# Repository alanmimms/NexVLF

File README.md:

# NexVLF
This is software defined radio hardware and software for VLF 40kHz to
300kHz range with high noise immunity, dynamic range, sensitivity, and
a built in 1m diameter loop antenna. It could be used to fool around
with VLF, to add a WWVB decoder to your shack (one is planned in
software), or whatever you like.

# Architecture

NexVLF uses an STM32H753 microcontroller to control and shovel bits
from the AK5572 24-bit audio codec into a USB2 (480Mb/s "high speed")
audio interface. A host CPU runs an app built for Linux, MacOS, and
Windows supplying the DSP functions to demodulate and tune the SDR
samples and a flexible and easily extensible receiver GUI mostly
written in Lua.

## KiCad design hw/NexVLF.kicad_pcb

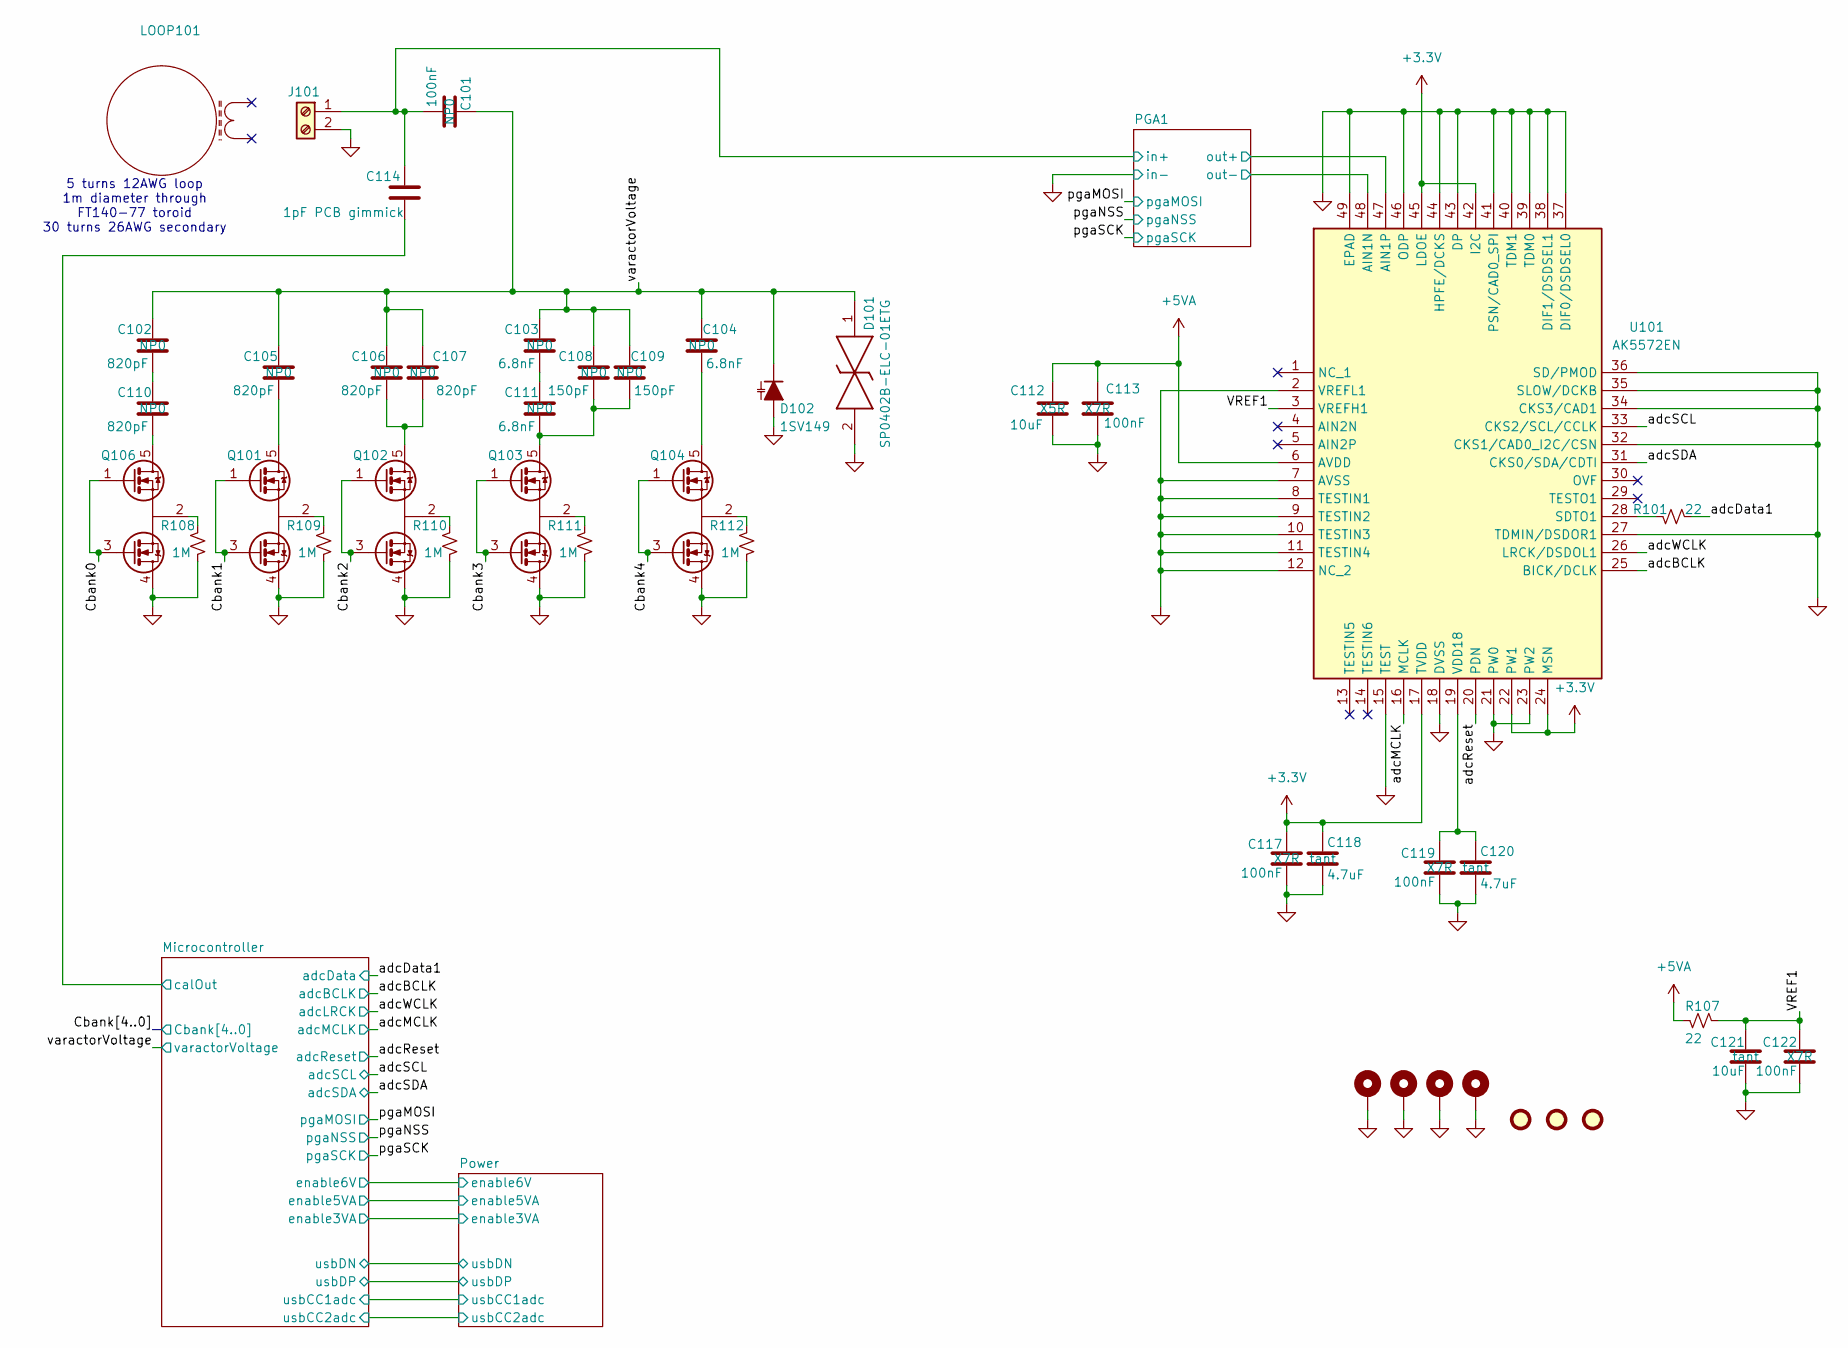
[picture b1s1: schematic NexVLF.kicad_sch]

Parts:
C101: 100nF; C_1206_3216Metric; MPN GRM3195C2A104JA01D; LCSC_PN C170182
C102, C105, C106, C107, C110: 820pF; C_1206_3216Metric; MPN GRM3195C2A104JA01D; LCSC_PN C170182
C103, C104, C111: 6.8nF; C_1206_3216Metric; MPN GRM3195C2A104JA01D; LCSC_PN C170182
C108, C109: 150pF; C_1206_3216Metric; MPN GRM3195C2A104JA01D; LCSC_PN C170182
C112: 10uF; C_0402_1005Metric; MPN GRM155R61E105KE11D; LCSC_PN C301928
C113, C117, C119, C122: 100nF; C_0402_1005Metric; MPN C0805F104K1RACAUTO; LCSC_PN C24452
C114: 1pF PCB gimmick; PCB-gimmick-1pF
C118, C120: 4.7uF; C_0805_2012Metric; MPN 298D475X9010M2T; LCSC_PN C18535241
C121: 10uF; C_0805_2012Metric; MPN TAJD106K050RNJ; LCSC_PN C4983748
D101: SP0402B-ELC-01ETG; D_0402_1005Metric; MPN SP0402B-ELC-01ETG; LCSC_PN C1974049
D102: 1SV149; TO-92-2
FID101, FID102, FID103: Fiducial; Fiducial_0.5mm_Mask1.5mm
H101, H102, H103, H104: MountingHole_Pad; MountingHole_3.2mm_M3_DIN965_Pad
J101: ANT; Altech_AK300_1x02_P5.00mm_45-Degree
LOOP101: (no value)
Q101, Q102, Q103, Q104, Q106: DMN32D2LDF; SOT-353_SC-70-5
R101, R107: 22; R_0402_1005Metric; JLCPCBpn C4258780
R108, R109, R110, R111, R112: 1M; R_0402_1005Metric; JLCPCBpn C4258780
U101: AK5572EN; QFN50P700X700X100-49N-D; Mouser Part Number 412-AK5572EN

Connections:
+3.3V: C117.2, C118.2, U101.17 (TVDD), U101.22 (PW1), U101.24 (MSN), U101.42 (I2C), U101.45 (LDOE); also elsewhere on the board
+5VA: C112.1, C113.1, R107.2, U101.6 (AVDD); also elsewhere on the board
/Cbank0: Q106.1 (G1), Q106.3 (G2); also elsewhere on the board
/Cbank1: Q101.1 (G1), Q101.3 (G2); also elsewhere on the board
/Cbank2: Q102.1 (G1), Q102.3 (G2); also elsewhere on the board
/Cbank3: Q103.1 (G1), Q103.3 (G2); also elsewhere on the board
/Cbank4: Q104.1 (G1), Q104.3 (G2); also elsewhere on the board
/PGA1/in+: C101.2, C114.1, J101.1; also elsewhere on the board
/PGA1/out+: U101.47 (AIN1P); also elsewhere on the board
/PGA1/out-: U101.48 (AIN1N); also elsewhere on the board
/VREF1: C121.1, C122.1, R107.1, U101.3 (VREFH1)
/adcBCLK: U101.25 (BICK/DCLK); also elsewhere on the board
/adcData1: R101.1; also elsewhere on the board
/adcMCLK: U101.16 (MCLK); also elsewhere on the board
/adcReset: U101.20 (PDN); also elsewhere on the board
/adcSCL: U101.33 (CKS2/SCL/CCLK); also elsewhere on the board
/adcSDA: U101.31 (CKS0/SDA/CDTI); also elsewhere on the board
/adcWCLK: U101.26 (LRCK/DSDOL1); also elsewhere on the board
/varactorVoltage: C101.1, C102.1, C103.1, C104.1, C105.1, C106.1, C107.1, C108.1, C109.1, D101.1, D102.1 (K); also elsewhere on the board
GND: C112.2, C113.2, C117.1, C118.1, C119.1, C120.1, C121.2, C122.2, D101.2, D102.2 (A), H101.1, H102.1, H103.1, H104.1, J101.2, Q101.4 (D2), Q102.4 (D2), Q103.4 (D2), Q104.4 (D2), Q106.4 (D2), R108.2, R109.2, R110.2, R111.2, R112.2, U101.2 (VREFL1), U101.7 (AVSS), U101.8 (TESTIN1), U101.9 (TESTIN2), U101.10 (TESTIN3), U101.11 (TESTIN4), U101.12 (NC_2), U101.15 (TEST), U101.18 (DVSS), U101.21 (PW0), U101.23 (PW2), U101.27 (TDMIN/DSDOR1), U101.32 (CKS1/CAD0_I2C/CSN), U101.34 (CKS3/CAD1), U101.35 (SLOW/DCKB), U101.36 (SD/PMOD), U101.37 (DIF0/DSDSEL0), U101.38 (DIF1/DSDSEL1), U101.39 (TDM0), U101.40 (TDM1), U101.41 (PSN/CAD0_SPI), U101.43 (DP), U101.44 (HPFE/DCKS), U101.46 (ODP), U101.49 (EPAD); also elsewhere on the board
unnamed: C102.2, C110.1
unnamed: C103.2, C111.1
unnamed: C105.2, Q101.5 (D1)
unnamed: Q101.2 (S), R109.1
unnamed: C106.2, C107.2, Q102.5 (D1)
unnamed: Q102.2 (S), R110.1
unnamed: C108.2, C109.2, C111.2, Q103.5 (D1)
unnamed: Q103.2 (S), R111.1
unnamed: C104.2, Q104.5 (D1)
unnamed: Q104.2 (S), R112.1
unnamed: C110.2, Q106.5 (D1)
unnamed: Q106.2 (S), R108.1
unnamed: R101.2, U101.28 (SDTO1)
unnamed: C119.2, C120.2, U101.19 (VDD18)

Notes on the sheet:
5 turns 12AWG loop 1m diameter through FT140-77 toroid 30 turns 26AWG secondary

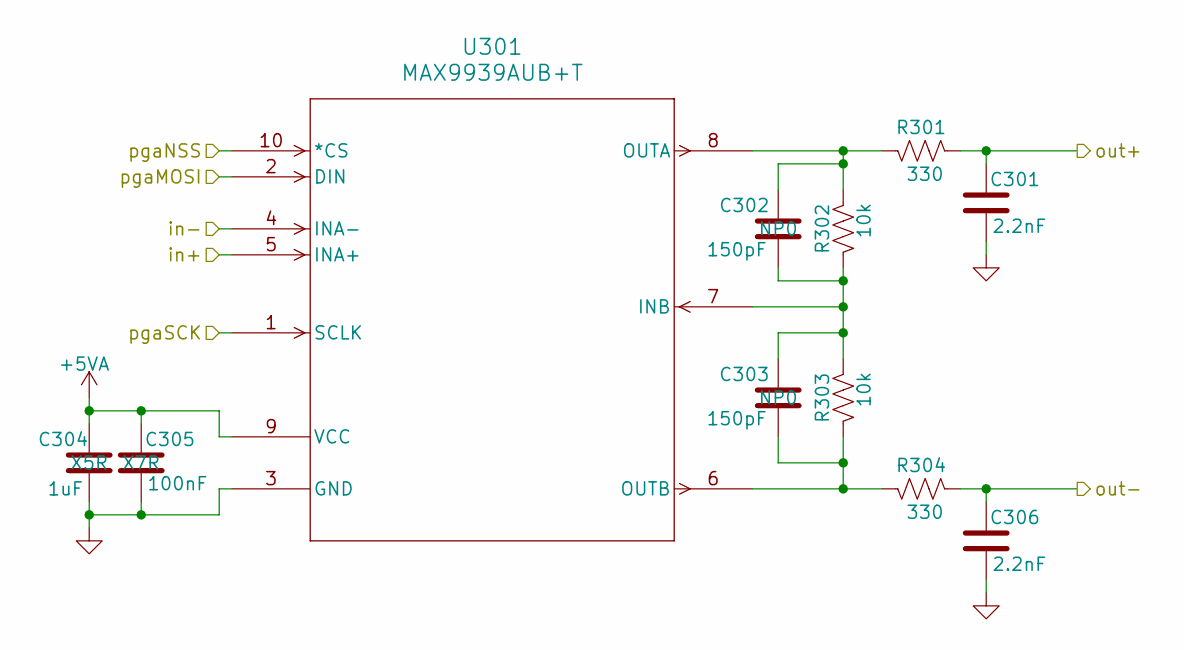
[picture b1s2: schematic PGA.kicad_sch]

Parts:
C301, C306: 2.2nF; C_0603_1608Metric
C302, C303: 150pF; C_0603_1608Metric; MPN 06033A151FAT2A; LCSC_PN C107038
C304: 1uF; C_0402_1005Metric; MPN GRM155R61E105KE11D; LCSC_PN C301928
C305: 100nF; C_0402_1005Metric; MPN C0805F104K1RACAUTO; LCSC_PN C24452
R301, R304: 330; R_0402_1005Metric; LCSC_PN C854274
R302, R303: 10k; R_0402_1005Metric; JLCPCBpn C723366
U301: MAX9939AUB+T; SOP50P490X110-10N; LCSC_PN C2057611

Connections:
+5VA: C304.1, C305.1, U301.9 (VCC); also elsewhere on the board
/PGA1/in+: U301.5 (INA+); also elsewhere on the board
/PGA1/out+: C301.1, R301.2; also elsewhere on the board
/PGA1/out-: C306.1, R304.2; also elsewhere on the board
/pgaMOSI: U301.2 (DIN); also elsewhere on the board
/pgaNSS: U301.10 (*CS); also elsewhere on the board
/pgaSCK: U301.1 (SCLK); also elsewhere on the board
GND: C301.2, C304.2, C305.2, C306.2, U301.3 (GND), U301.4 (INA-); also elsewhere on the board
unnamed: C302.2, C303.1, R302.2, R303.1, U301.7 (INB)
unnamed: C302.1, R301.1, R302.1, U301.8 (OUTA)
unnamed: C303.2, R303.2, R304.1, U301.6 (OUTB)

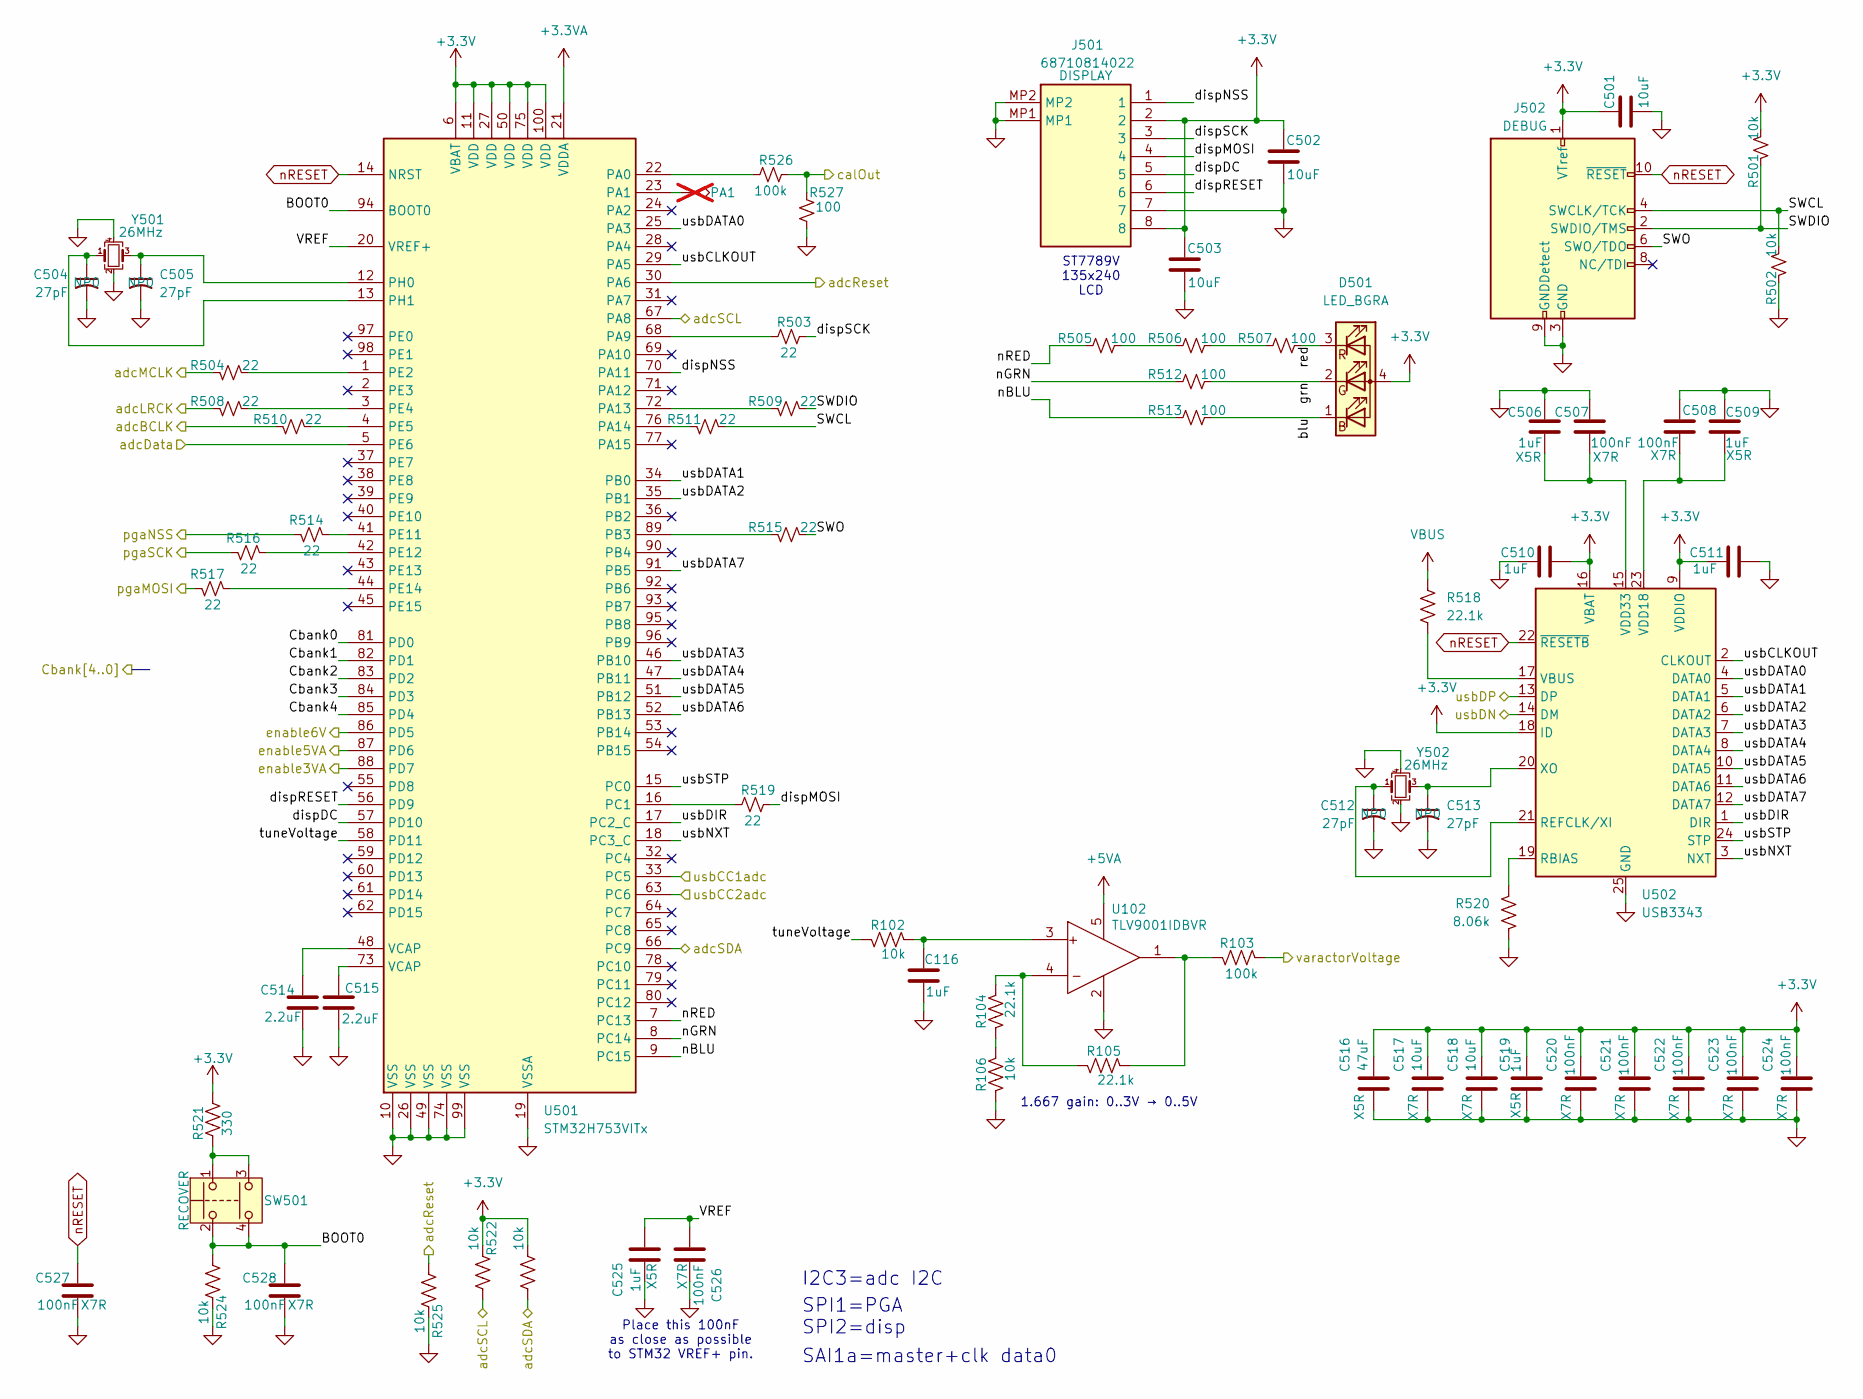
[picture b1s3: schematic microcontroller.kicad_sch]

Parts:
C116, C506, C509, C510, C511: 1uF; C_0402_1005Metric; Manufacturer_Part_Number GRM155R61E105KE11D; Mouser Part Number 81-GRM155R61E105KE1D
C501, C503: 10uF; C_0603_1608Metric; MPN 81-GXT155R71E223KE1D; LCSC_PN C327087
C502, C517, C518: 10uF; C_0603_1608Metric; Manufacturer_Part_Number 81-GXT155R71E223KE1D; Mouser Part Number 963-MLAST168BB5106MT
C504: 27pF; C_0402_1005Metric; LCSC_PN C107045
C505, C512, C513: 27pF; C_0402_1005Metric; JLCPCBpn C107045
C507, C508, C524: 100nF; C_0402_1005Metric; MPN C0805F104K1RACAUTO; LCSC_PN C24452
C514, C515: 2.2uF; C_0603_1608Metric; LCSC_PN C100082
C516: 47uF; C_1206_3216Metric; MPN TCTAL1A107M8R-V1; LCSC_PN C403725
C519, C525: 1uF; C_0402_1005Metric; MPN GRM155R61E105KE11D; LCSC_PN C301928
C520, C521, C522, C523, C526, C527, C528: 100nF; C_0402_1005Metric
D501: LED_BGRA; UHD111AFKAC3K23E1L3VG5ZB3Z3; MPN UHD111A-FKA-C3K23E1L3VG5ZB3Z3; Mouser_PN 941-UHD1AA3K3E3V53Z3
J501: 68710814022; MPN 5034800800; LCSC_PN C293338
J502: FTSH-105-01-L-DV-K; FTSH10501LDVK; LCSC_PN C5155080
PG501: PA1; TestPoint_Pad_1.0x1.0mm; not fitted
R102, R106: 10k; R_0402_1005Metric; JLCPCBpn C723366
R103: 100k; R_0402_1005Metric; LCSC_PN C728576
R104, R105: 22.1k; R_0402_1005Metric; JLCPCBpn C723366
R501, R502, R522, R523, R524, R525: 10k; R_0402_1005Metric; LCSC_PN C723366
R503, R504, R508, R509, R511, R514, R515, R516, R517, R519: 22; R_0402_1005Metric; JLCPCBpn C4258780
R505, R506, R507, R512, R513: 100; R_0402_1005Metric
R510: 22; R_0402_1005Metric; LCSC_PN C4258780
R518: 22.1k; R_0402_1005Metric; LCSC_PN C284424
R520: 8.06k; R_0402_1005Metric; LCSC_PN C863964
R521: 330; R_0402_1005Metric; LCSC_PN C723366
R526: 100k; R_0402_1005Metric; JLCPCBpn C4258780
R527: 100; R_0402_1005Metric; JLCPCBpn C4258780
SW501: Push button switch; EVQPUC02K
U102: TLV9001IDBVR; SOT95P280X145-5N; Mouser Part Number 595-TLV9001IDBVR
U501: STM32H753VITx; LQFP-100_14x14mm_P0.5mm; LCSC_PN C730206
U502: USB3343; QFN-24-1EP_4x4mm_P0.5mm_EP2.6x2.6mm; MPN USB3343-CP-TR; LCSC_PN C633347
Y501, Y502: 26MHz; Crystal_SMD_2520-4Pin_2.5x2.0mm; MPN E2X260181G01; LCSC_PN C712894

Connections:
+3.3V: C501.2, C502.2, C503.2, C510.2, C511.1, C516.1, C517.1, C518.1, C519.1, C520.1, C521.1, C522.1, C523.1, C524.1, D501.4 (A), J501.2, J501.8, J502.1 (VTref), R501.1, R521.1, R522.1, R523.1, U501.6 (VBAT), U501.11 (VDD), U501.27 (VDD), U501.50 (VDD), U501.75 (VDD), U501.100 (VDD), U502.9 (VDDIO), U502.16 (VBAT), U502.18 (ID); also elsewhere on the board
+3.3VA: U501.21 (VDDA); also elsewhere on the board
+5VA: U102.5 (V+); also elsewhere on the board
/Cbank0: U501.81 (PD0); also elsewhere on the board
/Cbank1: U501.82 (PD1); also elsewhere on the board
/Cbank2: U501.83 (PD2); also elsewhere on the board
/Cbank3: U501.84 (PD3); also elsewhere on the board
/Cbank4: U501.85 (PD4); also elsewhere on the board
/Microcontroller/BOOT0: C528.1, R524.1, SW501.2, SW501.4, U501.94 (BOOT0)
/Microcontroller/SWCL: J502.4 (SWCLK/TCK), R502.1, R511.1
/Microcontroller/SWDIO: J502.2 (SWDIO/TMS), R501.2, R509.1
/Microcontroller/SWO: J502.6 (SWO/TDO), R515.1
/Microcontroller/VREF: C525.1, C526.1, U501.20 (VREF+)
/Microcontroller/blu: D501.1 (BK), R513.2
/Microcontroller/calOut: R526.2, R527.2
/Microcontroller/dispDC: J501.5, U501.57 (PD10)
/Microcontroller/dispMOSI: J501.4, R519.2
/Microcontroller/dispNSS: J501.1, U501.70 (PA11)
/Microcontroller/dispRESET: J501.6, U501.56 (PD9)
/Microcontroller/dispSCK: J501.3, R503.2
/Microcontroller/enable3VA: U501.88 (PD7); also elsewhere on the board
/Microcontroller/enable5VA: U501.87 (PD6); also elsewhere on the board
/Microcontroller/enable6V: U501.86 (PD5); also elsewhere on the board
/Microcontroller/grn: D501.2 (GK), R512.2
/Microcontroller/nBLU: R513.1, U501.9 (PC15)
/Microcontroller/nGRN: R512.1, U501.8 (PC14)
/Microcontroller/nRED: R505.1, U501.7 (PC13)
/Microcontroller/red: D501.3 (RK), R507.2
/Microcontroller/tuneVoltage: R102.2, U501.58 (PD11)
/Microcontroller/usbCC1adc: U501.33 (PC5); also elsewhere on the board
/Microcontroller/usbCC2adc: U501.63 (PC6); also elsewhere on the board
/Microcontroller/usbCLKOUT: U501.29 (PA5), U502.2 (CLKOUT)
/Microcontroller/usbDATA0: U501.25 (PA3), U502.4 (DATA0)
/Microcontroller/usbDATA1: U501.34 (PB0), U502.5 (DATA1)
/Microcontroller/usbDATA2: U501.35 (PB1), U502.6 (DATA2)
/Microcontroller/usbDATA3: U501.46 (PB10), U502.7 (DATA3)
/Microcontroller/usbDATA4: U501.47 (PB11), U502.8 (DATA4)
/Microcontroller/usbDATA5: U501.51 (PB12), U502.10 (DATA5)
/Microcontroller/usbDATA6: U501.52 (PB13), U502.11 (DATA6)
/Microcontroller/usbDATA7: U501.91 (PB5), U502.12 (DATA7)
/Microcontroller/usbDIR: U501.17 (PC2_C), U502.1 (DIR)
/Microcontroller/usbDN: U502.14 (DM); also elsewhere on the board
/Microcontroller/usbDP: U502.13 (DP); also elsewhere on the board
/Microcontroller/usbNXT: U501.18 (PC3_C), U502.3 (NXT)
/Microcontroller/usbSTP: U501.15 (PC0), U502.24 (STP)
/adcBCLK: R510.2; also elsewhere on the board
/adcData1: U501.5 (PE6); also elsewhere on the board
/adcMCLK: R504.2; also elsewhere on the board
/adcReset: R525.1, U501.30 (PA6); also elsewhere on the board
/adcSCL: R522.2, U501.67 (PA8); also elsewhere on the board
/adcSDA: R523.2, U501.66 (PC9); also elsewhere on the board
/adcWCLK: R508.2; also elsewhere on the board
/pgaMOSI: R517.2; also elsewhere on the board
/pgaNSS: R514.2; also elsewhere on the board
/pgaSCK: R516.2; also elsewhere on the board
/varactorVoltage: R103.1; also elsewhere on the board
GND: C116.1, C501.1, C502.1, C503.1, C504.2, C505.2, C506.2, C507.1, C508.1, C509.2, C510.1, C511.2, C512.2, C513.2, C514.2, C515.2, C516.2, C517.2, C518.2, C519.2, C520.2, C521.2, C522.2, C523.2, C524.2, C525.2, C526.2, C527.2, C528.2, J501.7, J501.MP1, J501.MP2, J502.3 (GND), J502.5 (GND), J502.9 (GNDDetect), R106.2, R502.2, R520.2, R524.2, R525.2, R527.1, U102.2 (V-), U501.10 (VSS), U501.19 (VSSA), U501.26 (VSS), U501.49 (VSS), U501.74 (VSS), U501.99 (VSS), U502.25 (GND), Y501.2, Y501.4, Y502.2, Y502.4; also elsewhere on the board
unnamed: C514.1, U501.48 (VCAP)
unnamed: C515.1, U501.73 (VCAP)
unnamed: R104.2, R106.1
unnamed: R505.2, R506.1
unnamed: R506.2, R507.1
unnamed: R521.2, SW501.1, SW501.3
unnamed: C116.2, R102.1, U102.3 (IN+)
unnamed: R104.1, R105.2, U102.4 (IN-)
unnamed: R103.2, R105.1, U102.1 (OUT)
unnamed: R526.1, U501.22 (PA0)
unnamed: PG501.1, U501.23 (PA1)
unnamed: R503.1, U501.68 (PA9)
unnamed: R509.2, U501.72 (PA13)
unnamed: R511.2, U501.76 (PA14)
unnamed: R515.2, U501.89 (PB3)
unnamed: R519.1, U501.16 (PC1)
unnamed: R504.1, U501.1 (PE2)
unnamed: R508.1, U501.3 (PE4)
unnamed: R510.1, U501.4 (PE5)
unnamed: R514.1, U501.41 (PE11)
unnamed: R516.1, U501.42 (PE12)
unnamed: R517.1, U501.44 (PE14)
unnamed: C505.1, U501.12 (PH0), Y501.3
unnamed: C504.1, U501.13 (PH1), Y501.1
unnamed: R520.1, U502.19 (RBIAS)
unnamed: C512.1, U502.21 (REFCLK/XI), Y502.1
unnamed: R518.2, U502.17 (VBUS)
unnamed: C508.2, C509.1, U502.23 (VDD18)
unnamed: C506.1, C507.2, U502.15 (VDD33)
unnamed: C513.1, U502.20 (XO), Y502.3
VBUS: R518.1; also elsewhere on the board
nRESET: C527.1, J502.10 (~RESET), U501.14 (NRST), U502.22 (~RESETB)

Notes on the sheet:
SPI1=PGA SPI2=disp
SAI1a=master+clk data0
1.667 gain: 0..3V → 0..5V
Place this 100nF as close as possible to STM32 VREF+ pin.
I2C3=adc I2C
ST7789V 135x240 LCD

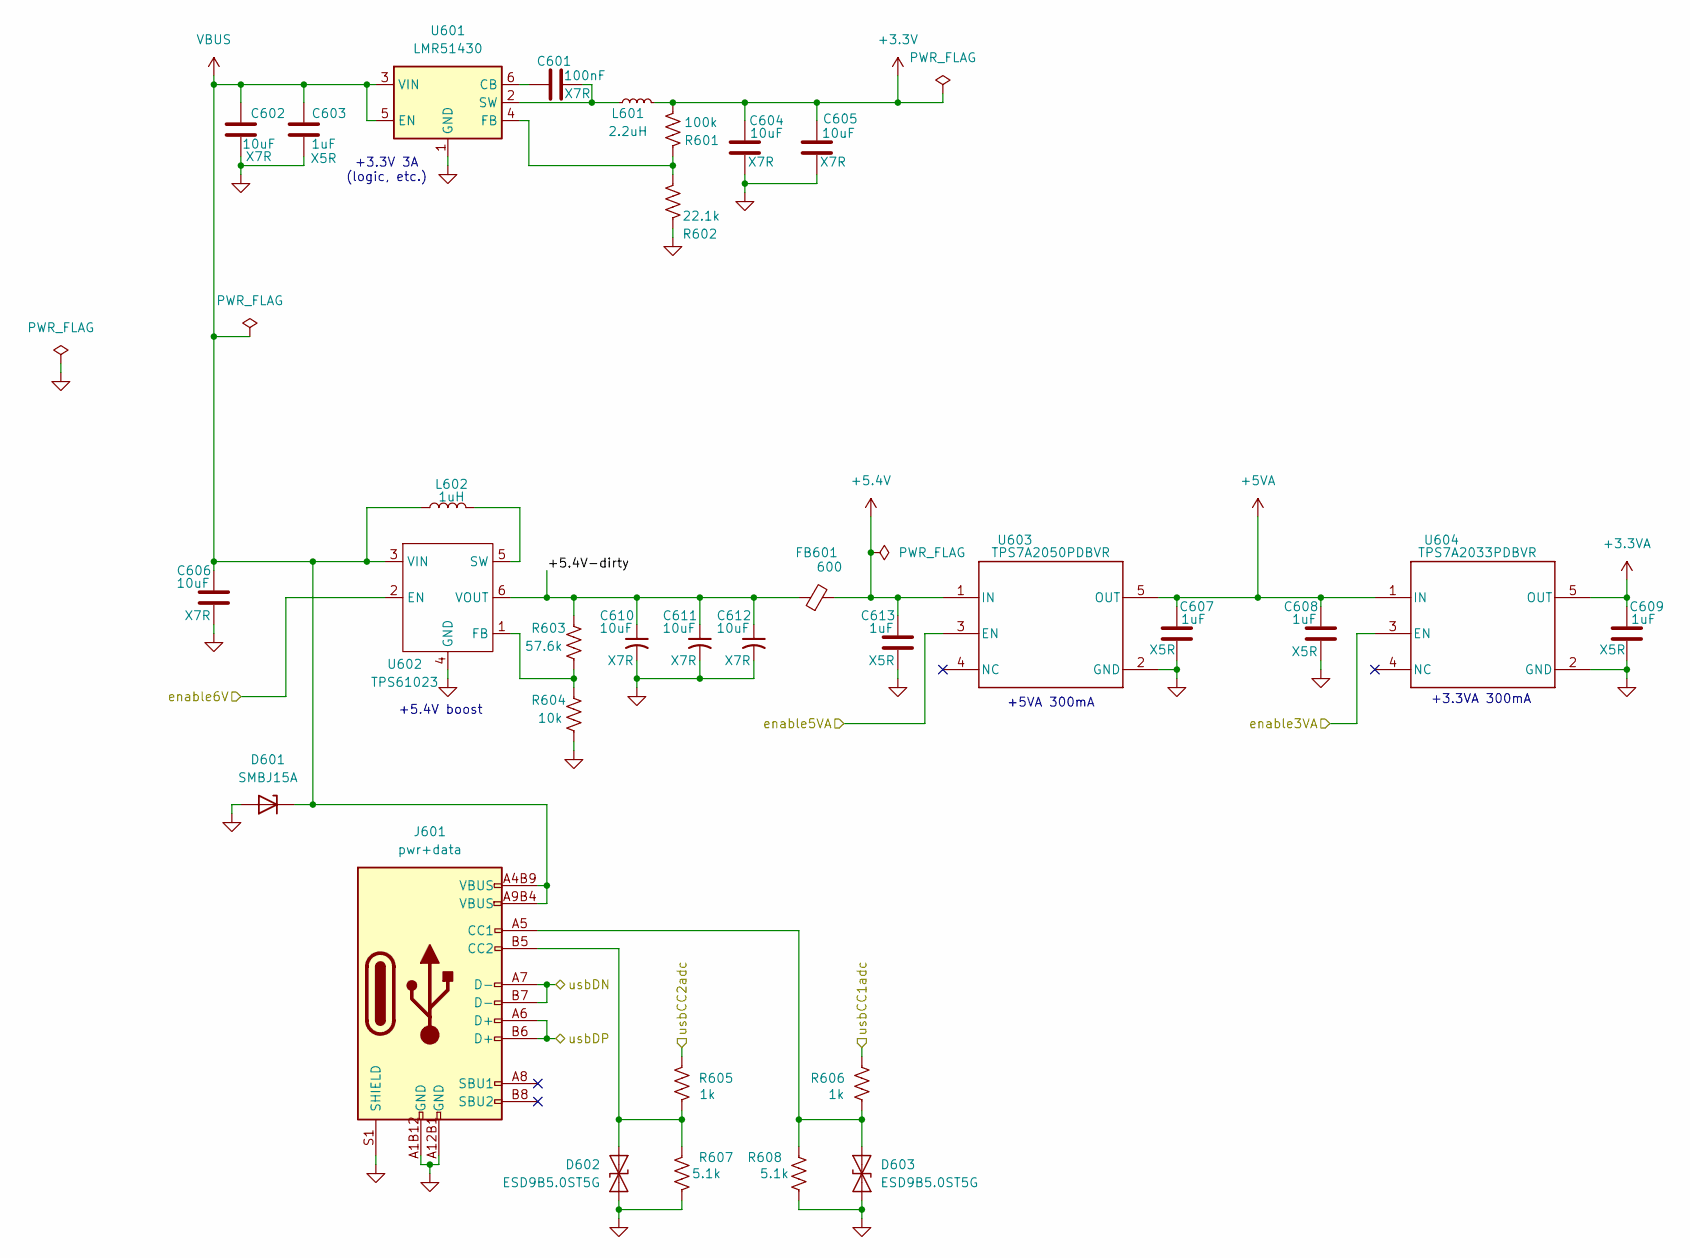
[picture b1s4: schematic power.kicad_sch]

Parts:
C601: 100nF; C_0402_1005Metric; MPN C0805F104K1RACAUTO; LCSC_PN C24452
C602, C606, C612: 10uF; C_0603_1608Metric; MPN 81-GXT155R71E223KE1D; LCSC_PN C327087
C603, C607, C613: 1uF; C_0402_1005Metric; MPN GRM155R61E105KE11D; LCSC_PN C301928
C604, C605, C610, C611: 10uF; C_0603_1608Metric; Manufacturer_Part_Number 81-GXT155R71E223KE1D; Mouser Part Number 963-MLAST168BB5106MT
C608, C609: 1uF; C_0402_1005Metric; Manufacturer_Part_Number GRM155R61E105KE11D; Mouser Part Number 81-GRM155R61E105KE1D
D601: SMBJ15A; D_SMB; MPN SMBJ15A; LCSC_PN C83846
D602, D603: ESD9B5.0ST5G; D_SOD-923; LCSC_PN C111566
FB601: 600; L_0603_1608Metric; MPN MI0603J601R-10; LCSC_PN C2441365
J601: pwr+data; USB_C_Receptacle_HRO_TYPE-C-31-M-12-bursted; MPN TYPE-C-31-M-12; LCSC_PN C165948
L601: 2.2uH; L_0805_2012Metric; Part Number LQM21PN2R2NGCD; LCSC_PN C86089
L602: 1uH; IND_XGL4030_COC; MPN XGL4030-102MEC; LCSC_PN C6336766
R601: 100k; R_0402_1005Metric; LCSC_PN C728576
R602: 22.1k; R_0402_1005Metric; LCSC_PN C284424
R603: 57.6k; R_0402_1005Metric; LCSC_PN C517765
R604: 10k; R_0402_1005Metric; LCSC_PN C723366
R605, R606: 1k; R_0402_1005Metric; LCSC_PN C136974
R607, R608: 5.1k; R_0402_1005Metric; LCSC_PN C854378
U601: LMR51430; SOT-23-6; LCSC_PN C5185863
U602: TPS61023; SOT-563; LCSC_PN C919459
U603: TPS7A2050PDBVR; DBV0005A-MFG; LCSC_PN C36907702
U604: TPS7A2033PDBVR; DBV0005A-MFG; LCSC_PN C36907702

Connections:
+3.3V: C604.1, C605.1, L601.2, R601.2; also elsewhere on the board
+3.3VA: C609.1, U604.5 (OUT); also elsewhere on the board
+5.4V: C613.1, FB601.2, U603.1 (IN)
+5VA: C607.1, C608.1, U603.5 (OUT), U604.1 (IN); also elsewhere on the board
/Microcontroller/enable3VA: U604.3 (EN); also elsewhere on the board
/Microcontroller/enable5VA: U603.3 (EN); also elsewhere on the board
/Microcontroller/enable6V: U602.2 (EN); also elsewhere on the board
/Microcontroller/usbCC1adc: R606.1; also elsewhere on the board
/Microcontroller/usbCC2adc: R605.1; also elsewhere on the board
/Microcontroller/usbDN: J601.A7 (D-), J601.B7 (D-); also elsewhere on the board
/Microcontroller/usbDP: J601.A6 (D+), J601.B6 (D+); also elsewhere on the board
/Power/+5.4V-dirty: C610.1, C611.1, C612.1, FB601.1, R603.2, U602.6 (VOUT)
GND: C602.2, C603.2, C604.2, C605.2, C606.2, C607.2, C608.2, C609.2, C610.2, C611.2, C612.2, C613.2, D601.2 (A), D602.1 (A1), D603.1 (A1), J601.A1B12 (GND), J601.A12B1 (GND), J601.S1 (SHIELD), R602.1, R604.1, R607.2, R608.2, U601.1 (GND), U602.4 (GND), U603.2 (GND), U604.2 (GND); also elsewhere on the board
unnamed: D602.2 (A2), J601.B5 (CC2), R605.2, R607.1
unnamed: D603.2 (A2), J601.A5 (CC1), R606.2, R608.1
unnamed: C601.1, U601.6 (CB)
unnamed: R601.1, R602.2, U601.4 (FB)
unnamed: C601.2, L601.1, U601.2 (SW)
unnamed: R603.1, R604.2, U602.1 (FB)
unnamed: L602.2, U602.5 (SW)
VBUS: C602.1, C603.1, C606.1, D601.1 (K), J601.A4B9 (VBUS), J601.A9B4 (VBUS), L602.1, U601.3 (VIN), U601.5 (EN), U602.3 (VIN); also elsewhere on the board

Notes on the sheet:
+3.3V 3A (logic, etc.)
+5.4V boost
+3.3VA 300mA
+5VA 300mA

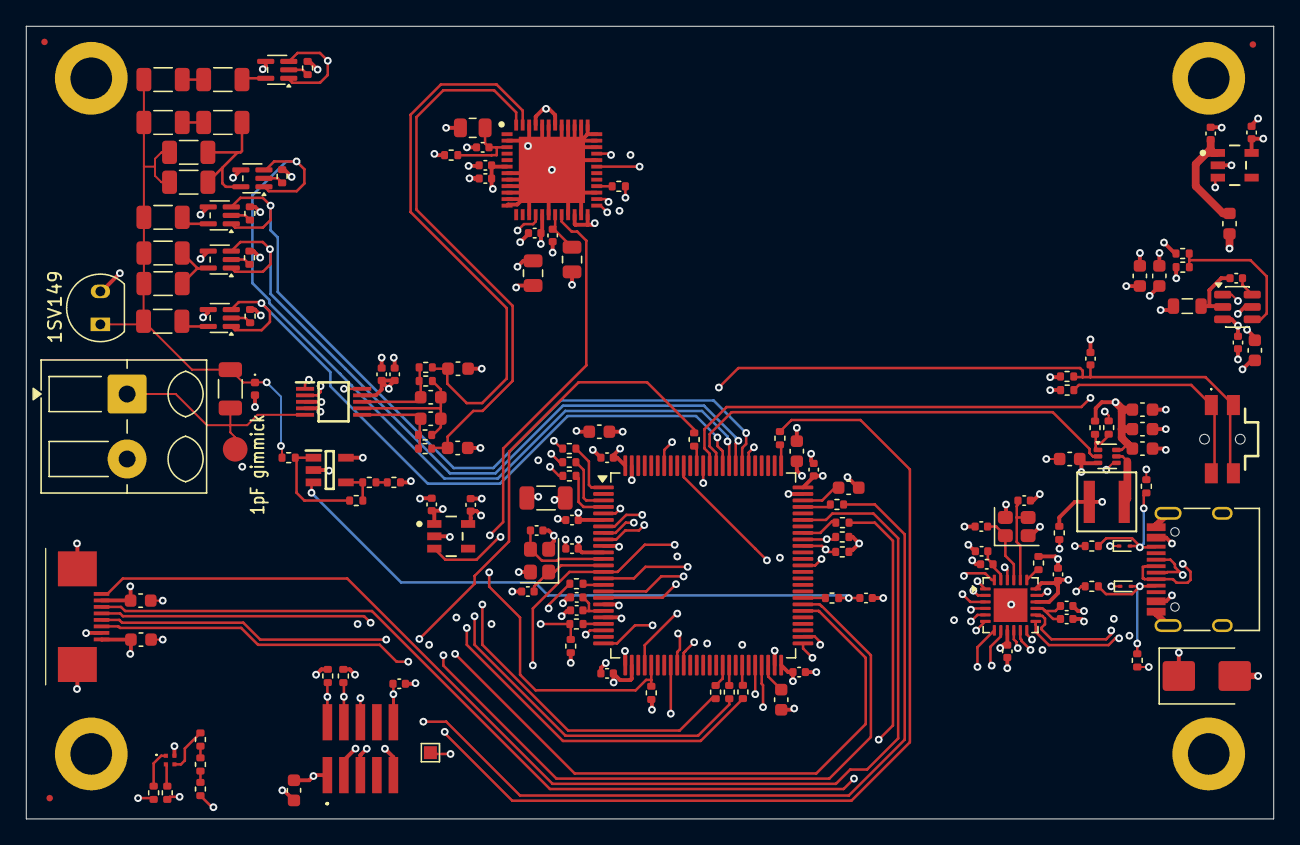
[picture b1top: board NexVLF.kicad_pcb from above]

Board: 6 copper layers, 96.0 x 61.0 mm, 156 parts (0 on the bottom side), 119 nets.

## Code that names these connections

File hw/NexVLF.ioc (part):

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Mcu.Name=STM32H753VITx
Mcu.Package=LQFP100
Mcu.UserName=STM32H753VITx
PA11.GPIOParameters=GPIO_Label
PA11.GPIO_Label=dispNSS
PA11.Mode=NSS_Signal_Hard_Output
PA11.Signal=SPI2_NSS
PA3.GPIOParameters=GPIO_Label
PA3.GPIO_Label=usbDATA0
PA3.Mode=Device_HS
PA3.Signal=USB_OTG_HS_ULPI_D0
PA4.Signal=COMP_DAC11_group
PA5.GPIOParameters=GPIO_Label
PA5.GPIO_Label=usbCLKOUT
PA5.Mode=Device_HS
PA5.Signal=USB_OTG_HS_ULPI_CK
PA8.GPIOParameters=GPIO_Label
PA8.GPIO_Label=audioSCL
PA8.Mode=I2C
PA8.Signal=I2C3_SCL
PA9.GPIOParameters=GPIO_Label
PA9.GPIO_Label=dispSCK
PA9.Mode=TX_Only_Simplex_Unidirect_Master
PA9.Signal=SPI2_SCK
PB0.GPIOParameters=GPIO_Label
PB0.GPIO_Label=usbDATA1
PB0.Mode=Device_HS
PB0.Signal=USB_OTG_HS_ULPI_D1
PB1.GPIOParameters=GPIO_Label
PB1.GPIO_Label=usbDATA2
PB1.Mode=Device_HS
PB1.Signal=USB_OTG_HS_ULPI_D2
PB10.GPIOParameters=GPIO_Label
PB10.GPIO_Label=usbDATA3
PB10.Mode=Device_HS
PB10.Signal=USB_OTG_HS_ULPI_D3
PB11.GPIOParameters=GPIO_Label
PB11.GPIO_Label=usbDATA4
PB11.Mode=Device_HS
PB11.Signal=USB_OTG_HS_ULPI_D4
PB12.GPIOParameters=GPIO_Label
PB12.GPIO_Label=usbDATA5
PB12.Mode=Device_HS
PB12.Signal=USB_OTG_HS_ULPI_D5
PB13.GPIOParameters=GPIO_Label
PB13.GPIO_Label=usbDATA6
PB13.Mode=Device_HS
PB13.Signal=USB_OTG_HS_ULPI_D6
PB5.GPIOParameters=GPIO_Label
PB5.GPIO_Label=usbDATA7
PB5.Mode=Device_HS
PB5.Signal=USB_OTG_HS_ULPI_D7
PC0.GPIOParameters=GPIO_Label
PC0.GPIO_Label=usbSTP
PC0.Mode=Device_HS
PC0.Signal=USB_OTG_HS_ULPI_STP
PC1.GPIOParameters=GPIO_Label
PC1.GPIO_Label=dispMOSI
PC1.Mode=TX_Only_Simplex_Unidirect_Master
PC1.Signal=SPI2_MOSI
PC2_C.GPIOParameters=GPIO_Label
PC2_C.GPIO_Label=usbDIR
PC2_C.Mode=Device_HS
PC2_C.Signal=USB_OTG_HS_ULPI_DIR
PC3_C.GPIOParameters=GPIO_Label
PC3_C.GPIO_Label=usbNXT
PC3_C.Mode=Device_HS
PC3_C.Signal=USB_OTG_HS_ULPI_NXT
PC5.GPIOParameters=GPIO_Label
PC5.GPIO_Label=usbCC1adc
PC5.Signal=GPIO_Analog
PC6.GPIOParameters=GPIO_Label
PC6.GPIO_Label=usbCC2adc
PC6.Signal=GPIO_Analog
PC9.GPIOParameters=GPIO_Label
PC9.GPIO_Label=audioSDA
PC9.Mode=I2C
PC9.Signal=I2C3_SDA
PD10.GPIOParameters=GPIO_Label
PD10.GPIO_Label=dispDC
PD10.Signal=GPIO_Output
PD5.GPIOParameters=GPIO_Label
PD5.GPIO_Label=enable6V
PD5.Signal=GPIO_Output
PD6.GPIOParameters=GPIO_Label
PD6.GPIO_Label=enable3V3
PD6.Signal=GPIO_Output
PD7.GPIOParameters=GPIO_Label
PD7.GPIO_Label=enable3VA
PD7.Signal=GPIO_Output
PD8.GPIOParameters=GPIO_Label
PD8.GPIO_Label=enable5VA
PD8.Signal=GPIO_Output
PD9.GPIOParameters=GPIO_Label
PD9.GPIO_Label=dispRESET
PD9.Signal=GPIO_Output
PE11.GPIOParameters=GPIO_Label
PE11.GPIO_Label=pgaNSS
PE11.Mode=NSS_Signal_Hard_Output
PE11.Signal=SPI4_NSS
PE12.GPIOParameters=GPIO_Label
PE12.GPIO_Label=pgaSCK
PE12.Mode=TX_Only_Simplex_Unidirect_Master
PE12.Signal=SPI4_SCK
PE14.GPIOParameters=GPIO_Label
PE14.GPIO_Label=pgaMOSI
PE14.Mode=TX_Only_Simplex_Unidirect_Master
PE14.Signal=SPI4_MOSI
PE2.GPIOParameters=GPIO_Speed,GPIO_Label
PE2.GPIO_Label=audioMCLK
PE2.GPIO_Speed=GPIO_SPEED_FREQ_LOW
PE2.Mode=SAI_A_MasterWithClock
PE2.Signal=SAI1_MCLK_A
PE4.GPIOParameters=GPIO_Label
PE4.GPIO_Label=audioWCLK
PE4.Mode=SAI_A_MasterWithClock
PE4.Signal=SAI1_FS_A
PE5.GPIOParameters=GPIO_Speed,GPIO_Label
PE5.GPIO_Label=audioBCLK
PE5.GPIO_Speed=GPIO_SPEED_FREQ_LOW
PE5.Mode=SAI_A_MasterWithClock
PE5.Signal=SAI1_SCK_A
PE6.GPIOParameters=GPIO_Label
PE6.GPIO_Label=audioData
PE6.Mode=SAI_A_MasterWithClock
PE6.Signal=SAI1_SD_A
PH0-OSC_IN\ (PH0).Mode=HSE-External-Clock-Source
PH0-OSC_IN\ (PH0).Signal=RCC_OSC_IN
RCC.SYSCLKFreq_VALUE=64000000
board=custom

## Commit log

2026-05-05 initial
2026-05-05 Add README
2026-05-05 Starting some layout
2026-05-07 Routing complete for DVT1 all ERC and DRC pass, 3D view is full
